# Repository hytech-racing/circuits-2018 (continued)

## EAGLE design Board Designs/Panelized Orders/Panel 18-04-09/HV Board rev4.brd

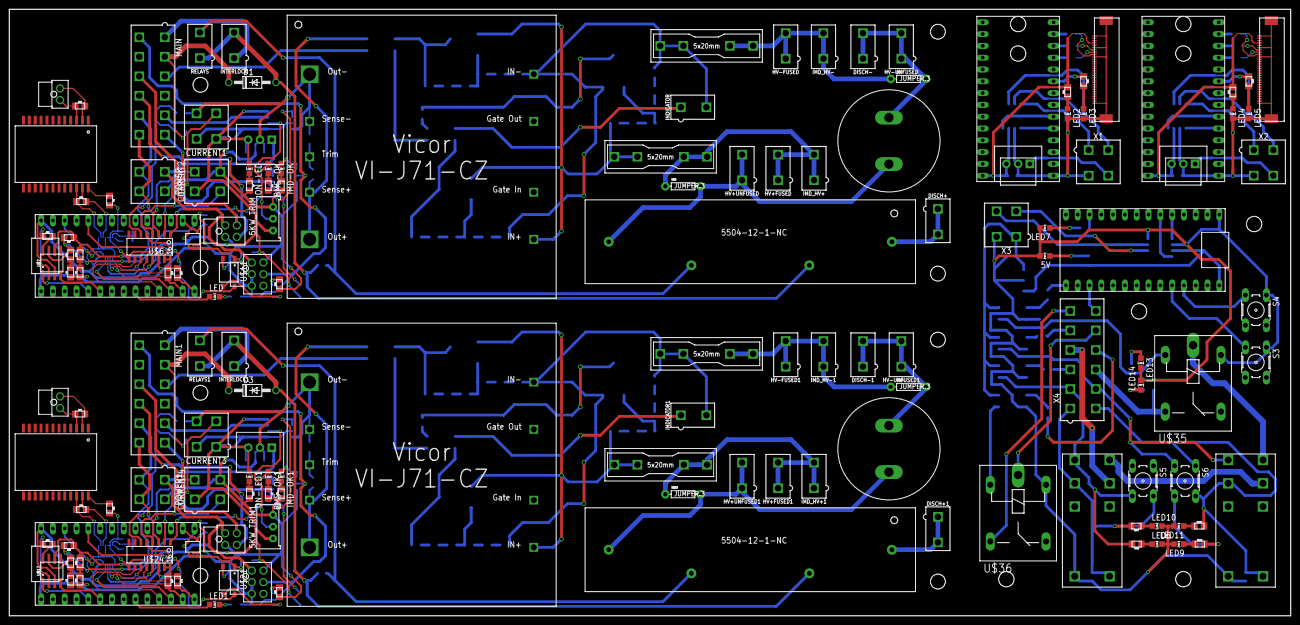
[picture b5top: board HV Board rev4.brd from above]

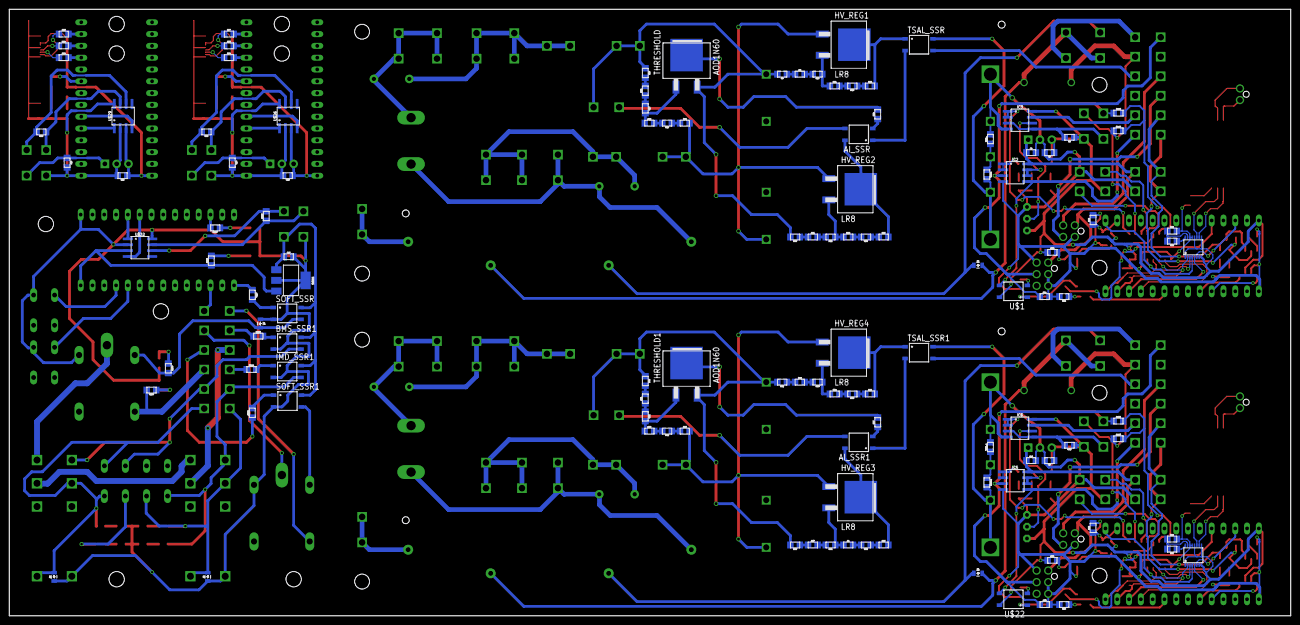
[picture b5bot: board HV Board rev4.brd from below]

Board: 2 copper layers, 275.8 x 130.6 mm, 262 parts (117 on the bottom side), 235 nets.

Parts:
5KW_TRIM, 5KW_TRIM1: TRIMPOT_3296
5V: LED-805
5VREG: SOT223
AI_SSR, AI_SSR1: CPC1002N; SOP04
BMS-OK, BMS-OK1: GREEN; LED-805
BMS_SSR1: CPC1002N; SOP04
C1, C6: 220uF; LLS2V221MELZ
C2, C3, C5, C12: 10uF; 0805
C4, C11: 27pF; 0805
C7, C8, C9, C10: 560pF; 0805
C13, C15: 0.1uF; 0805
C14, C16: 0.33uF; 0805
C17: .22uF; 0805
CURRENT1, CURRENT2, CURRENT3, CURRENT4: CONNECTOR-4; MINIFIT_5566-4
D1, D3: DIODE; DO-41
D2, D4, D5, D6, D7: DIODE0805; 0805_D
DISCH+, DISCH+1: DISCHARGE+; MINIFIT_5566-2
DISCH-, DISCH-1: DISCHARGE -; MINIFIT_5566-2
EM, EM1: CONNECTOR-4; NANO-FIT_VERTICAL-4
FUSE, FUSE1, FUSE2, FUSE3: 1A; 0751.0110
HV+FUSED, HV+FUSED1: FUSED+; MINIFIT_5566-2
HV+UNFUSED, HV+UNFUSED1: FSAE; MINIFIT_5566-2
HV-FUSED, HV-FUSED1: FUSED-; MINIFIT_5566-2
HV-UNFUSED, HV-UNFUSED1: FSAE; MINIFIT_5566-2
HV_REG1, HV_REG2, HV_REG3, HV_REG4: LR8; TO-252
IC1, IC4: OKI-78SR
IC2, IC3, IC5, IC6: NE5532SOIC; SOIC-08
IC7, IC8: TO-220
IMD, IMD1: CONNECTOR-6; NANO-FIT_VERTICAL-6
IMD-OK, IMD-OK1: YELLOW; LED-805
IMD_HV+, IMD_HV+1: IMD+; MINIFIT_5566-2
IMD_HV-, IMD_HV-1: IMD-; MINIFIT_5566-2
IMD_SSR1: CPC1002N; SOP04
INDICATOR, INDICATOR1: INDICATOR; MINIFIT_5566-2
INTERLOCK, INTERLOCK1: MINIFIT_5566-2
ISOSPI, ISOSPI1: CONNECTOR-2; NANO-FIT_VERTICAL-2
LED, LED1: BLUE; LED-805
LED2, LED3, LED4, LED5, LED6, LED7, LED9, LED10, LED11, LED13, LED14: LED-805
MAIN, MAIN1: CONNECTOR-12; MINIFIT_5566-12
ON-LED, ON-LED1: PURPLE; LED-805
POWER, POWER1: CONNECTOR-4; MINIFIT_5566-4
R1, R11, R12, R13, R23, R24, R25, R36, R37, R41, R48, R53, R54, R55, R56, R70, R71, R75: 2k; 0805
R2, R3, R4, R7: 820; 0805
R5, R44: 270; 0805
R6, R42, R43, R76: 10k; 0805
R8, R9, R10, R59, R60, R61: 8.2k; 0805
R14, R15, R16, R45, R49, R50: 510k; 0805
R17, R18, R19, R46, R51, R52, R118, R120: 43k; 0805
R20, R21, R22, R32, R57, R58: 20k; 0805
R26, R30, R33, R34, R47, R65, R67, R68: 1k; 0805
R27, R35, R62, R69, R80, R86, R113: 120; 0805
R28, R29, R40, R63, R64, R74: 100; 0805
R31, R66: 43; 0805
R38, R72: 430; 0805
R39, R73: 200; 0805
R77, R78, R79, R81, R82, R83, R84, R85, R87, R88, R105, R106, R107, R108, R109, R110, R111, R112, R114, R115, R116, R117: 0805
R119, R121: 12k; 0805
RELAYS, RELAYS1: MINIFIT_5566-2
S3, S4, S5, S6: B3F-10XX
SOFT_SSR, SOFT_SSR1: CPC1002N; SOP04
THRESHOLD, THRESHOLD1: AOD1N60; TO-252
TRIM+, TRIM+1: 0805
TRIM-, TRIM-1: 0805
TSAL_SSR, TSAL_SSR1: CPC1002N; SOP04
U$1, U$11, U$21, U$22: SOP04
U$2, U$23: SM51589PEL
U$3, U$4, U$15, U$16: JUMPER.3; AXIAL-0.3
U$5, U$14: HV_DCDC_VI-J71-CZ
U$6, U$24: MCP3208SOIC; SOIC-16
U$7, U$17, U$26, U$29, U$32: MCP2551; SOIC-08
U$8, U$18: LTC6820; MSOP-16
U$9, U$19, U$25, U$28, U$31: TEENSY_3.2_SIMPLE
U$10, U$20: STWD100; SOT23-5
U$12, U$13: 5504-12-1-NC
U$27, U$30: FFC-30P-0.5MM
U$33, U$34: G2RL-2-DC12; G2RL-2
U$35, U$36: G5LE; ZF112
X1, X2, X3: CONNECTOR-4; MINIFIT_5566-4
X4: CONNECTOR-12; MINIFIT_5566-12

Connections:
5KW_TRIG: 5KW_TRIM.2, IC3.6
5KW_TRIG1: 5KW_TRIM1.2, IC6.6
+3V1: U$18.6, U$19.3.3V
+3V3: U$8.6, U$9.3.3V
+5V: 5KW_TRIM.1, C3.1, CURRENT1.1, CURRENT2.1, IC1.3, IC3.8, ON-LED.A, R6.1, R36.1, R37.1, R38.1, U$1.4, U$6.5, U$6.15, U$6.16, U$7.3, U$8.1, U$8.7, U$8.8, U$8.9, U$8.12, U$9.VIN, U$10.VCC
+5V1: 5KW_TRIM1.1, C5.1, CURRENT3.1, CURRENT4.1, IC4.3, IC6.8, ON-LED1.A, R43.1, R70.1, R71.1, R72.1, U$17.3, U$18.1, U$18.7, U$18.8, U$18.9, U$18.12, U$19.VIN, U$20.VCC, U$22.4, U$24.5, U$24.15, U$24.16
+5V2: C13.1, IC7.3, R81.2, U$25.VIN, U$26.3, U$27.26, U$27.27
+5V3: C15.1, IC8.3, R87.2, U$28.VIN, U$29.3, U$30.26, U$30.27
+5V4: 5VREG.3, R106.1, U$31.VIN, U$32.3
+12V: C2.1, EM.P$1, IC1.1, IC2.8, IMD.P$1, POWER.1
+12V1: C12.1, EM1.P$1, IC4.1, IC5.8, IMD1.P$1, POWER1.1
+12V2: C14.1, IC7.1, X1.4
+12V3: C16.1, IC8.1, X2.4
+12V4: 5VREG.1, BMS_SSR1.4, C17.1, IMD_SSR1.4, SOFT_SSR.4, SOFT_SSR1.4, X3.1
BMS_12V: BMS_SSR1.3, R112.2, S6.3, S6.4, U$34.4, X4.8
BMS_INRLK: R116.1, X4.10
BMS_OK: IC2.5, MAIN.6, U$1.3
BMS_OK1: IC5.5, MAIN1.6, U$22.3
BMS_OK2: D6.C, R108.2, S6.1, S6.2, U$34.3, U$34.COIL-, X4.7
BMS_WATCH: U$1.1, U$11.3
BMS_WATCH1: U$21.3, U$22.1
BSPD_CUR_FAULT: IC3.7, MAIN.5
BSPD_CUR_FAULT1: IC6.7, MAIN1.5
BTN_X: S4.3, U$31.A9
BTN_Y: S3.3, U$31.A8
CANH: MAIN.12, POWER.4, R27.2, R28.2, U$7.7
CANH1: MAIN1.12, POWER1.4, R62.2, R63.2, U$17.7
CANH2: R80.1, U$26.7, X1.1
CANH3: R86.1, U$29.7, X2.1
CANH4: R113.1, U$32.7, X3.4
CANL: MAIN.11, POWER.3, R27.1, R29.2, U$7.6
CANL1: MAIN1.11, POWER1.3, R62.1, R64.2, U$17.6
CANL2: R80.2, U$26.6, X1.2
CANL3: R86.2, U$29.6, X2.2
CANL4: R113.2, U$32.6, X3.3
CANRX: U$25.D4(CANRX), U$26.4
CANRX1: U$28.D4(CANRX), U$29.4
CANRX2: U$31.D4(CANRX), U$32.4
CANTX: U$25.D3(CANTX), U$26.1
CANTX1: U$28.D3(CANTX), U$29.1
CANTX2: U$31.D3(CANTX), U$32.1
CS_LTC1: U$18.5, U$19.D10(TX2)
CS_LTC6820: U$8.5, U$9.D10(TX2)
CS_MCP1: U$19.D9(RX2), U$24.10
CS_MCP3208: U$6.10, U$9.D9(RX2)
CUR_SENSE_1: IC3.1, IC3.2, U$6.1
CUR_SENSE_1_RAW: CURRENT1.2, IC3.3, IC3.5, R6.2
CUR_SENSE_1_RAW1: CURRENT3.2, IC6.3, IC6.5, R43.2
CUR_SENSE_2: CURRENT2.2, U$6.3
CUR_SENSE_3: CURRENT4.2, U$24.3
CUR_SENSE_4: IC6.1, IC6.2, U$24.1
DISCHARGE_RELAY_GND: D2.A, RELAYS.2, U$12.COIL-
DISCHARGE_RELAY_GND1: D4.A, RELAYS1.2, U$13.COIL-
EM_IO1: EM.P$3, MAIN.9
EM_IO2: EM.P$4, MAIN.10
EM_IO3: EM1.P$3, MAIN1.9
EM_IO4: EM1.P$4, MAIN1.10
GND: 5KW_TRIM.3, C2.2, C3.2, C4.2, C8.1, C9.1, CURRENT1.4, CURRENT2.4, EM.P$2, IC1.2, IC2.4, IC3.4, IMD.P$2, IMD.P$3, IMD.P$4, POWER.2, R3.1, R4.2, R5.2, R30.1, R31.2, R34.2, R39.1, R41.2, R42.2, R119.1, TRIM-.2, U$5.8SENSE-, U$5.9VOUT-, U$6.9, U$6.14, U$7.2, U$8.13, U$8.14, U$9.GND, U$10.EN, U$10.GND, U$11.2
GND1: 5KW_TRIM1.3, C5.2, C7.1, C10.1, C11.2, C12.2, CURRENT3.4, CURRENT4.4, EM1.P$2, IC4.2, IC5.4, IC6.4, IMD1.P$2, IMD1.P$3, IMD1.P$4, POWER1.2, R2.1, R7.2, R44.2, R65.1, R66.2, R68.2, R73.1, R75.2, R76.2, R121.1, TRIM-1.2, U$14.8SENSE-, U$14.9VOUT-, U$17.2, U$18.13, U$18.14, U$19.GND, U$20.EN, U$20.GND, U$21.2, U$24.9, U$24.14
GND2: C13.2, C14.2, IC7.2, LED2.C, LED3.C, U$25.GND, U$26.2, U$26.8, U$27.1, U$27.21, U$27.25, U$27.30, U$27.PAD@0, U$27.PAD@1, X1.3
GND3: C15.2, C16.2, IC8.2, LED4.C, LED5.C, U$28.GND, U$29.2, U$29.8, U$30.1, U$30.21, U$30.25, U$30.30, U$30.PAD@0, U$30.PAD@1, X2.3
GND4: 5V.C, 5VREG.2, 5VREG.4, BMS_SSR1.2, C17.2, D5.A, D6.A, D7.A, IMD_SSR1.2, LED6.C, LED7.C, LED9.C, LED10.C, LED11.C, LED13.C, LED14.C, S3.1, S4.1, SOFT_SSR.2, SOFT_SSR1.2, U$31.GND, U$32.2, U$32.8, U$33.COIL+, U$34.COIL+, U$35.1, U$36.1, X3.2
GPIO: U$31.A1, X4.12
HV+FUSED: FUSE.L1, FUSE.L2, HV+FUSED.1, HV+FUSED.2, IMD_HV+.1, IMD_HV+.2, U$3.P$1
HV+FUSED1: FUSE2.L1, FUSE2.L2, HV+FUSED1.1, HV+FUSED1.2, IMD_HV+1.1, IMD_HV+1.2, U$15.P$1
HV+FUSED_1A: FUSE.R1, FUSE.R2, HV_REG1.1, HV_REG2.1, R14.2, U$5.1VIN+
HV+FUSED_1A1: FUSE2.R1, FUSE2.R2, HV_REG3.1, HV_REG4.1, R50.2, U$14.1VIN+
HV+UNFUSED_FSAE: C1.P$1, HV+UNFUSED.1, HV+UNFUSED.2, U$3.P$2, U$12.CONTACT1
HV+UNFUSED_FSAE1: C6.P$1, HV+UNFUSED1.1, HV+UNFUSED1.2, U$13.CONTACT1, U$15.P$2
HV+UNFUSED_FSAE_DISCHARGE: DISCH+.1, DISCH+.2, U$12.CONTACT2
HV+UNFUSED_FSAE_DISCHARGE1: DISCH+1.1, DISCH+1.2, U$13.CONTACT2
HV-FUSED: FUSE1.L1, FUSE1.L2, HV-FUSED.1, HV-FUSED.2, IMD_HV-.1, IMD_HV-.2, U$4.P$1
HV-FUSED1: FUSE3.L1, FUSE3.L2, HV-FUSED1.1, HV-FUSED1.2, IMD_HV-1.1, IMD_HV-1.2, U$16.P$1
HV-FUSED_1A: FUSE1.R1, FUSE1.R2, INDICATOR.2, R8.2, R19.1, R20.2, THRESHOLD.3, U$5.4VIN-
HV-FUSED_1A1: FUSE3.R1, FUSE3.R2, INDICATOR1.2, R46.1, R58.2, R61.2, THRESHOLD1.3, U$14.4VIN-
HV-UNFUSED_FSAE: C1.P$2, DISCH-.1, DISCH-.2, HV-UNFUSED.1, HV-UNFUSED.2, U$4.P$2
HV-UNFUSED_FSAE1: C6.P$2, DISCH-1.1, DISCH-1.2, HV-UNFUSED1.1, HV-UNFUSED1.2, U$16.P$2
IMD_12V: IMD_SSR1.3, R111.2, S5.3, S5.4, U$33.4, X4.2
IMD_OK: D5.C, R107.2, S5.1, S5.2, U$33.3, U$33.COIL-, X4.1
ISOSPI-M: ISOSPI.P$2, R40.1, U$2.3
ISOSPI-M1: ISOSPI1.P$2, R74.1, U$23.3
ISOSPI-P: ISOSPI.P$1, R40.2, U$2.2
ISOSPI-P1: ISOSPI1.P$1, R74.2, U$23.2
MISO: R37.2, U$6.12, U$8.3, U$9.D12
MISO1: R71.2, U$18.3, U$19.D12, U$24.12
MOSI: R36.2, U$6.11, U$8.2, U$9.D11
MOSI1: R70.2, U$18.2, U$19.D11, U$24.11
unnamed: AI_SSR.4, HV_REG2.2(TAB), R25.2
unnamed: HV_REG1.2(TAB), R13.2, TSAL_SSR.1
unnamed: ON-LED.C, R5.1
unnamed: R39.2, U$1.2
unnamed: AI_SSR.2, R26.1
unnamed: AI_SSR.1, TSAL_SSR.2
unnamed: AI_SSR.3, INDICATOR.1
unnamed: R8.1, R9.1
unnamed: R26.2, THRESHOLD.2(TAB)
unnamed: R14.1, R15.1
unnamed: R15.2, R16.2
unnamed: R17.1, R18.1
unnamed: R18.2, R19.2
unnamed: R9.2, R10.2
unnamed: HV_REG2.3, R22.1, R23.1
unnamed: R11.2, R12.2
unnamed: R12.1, R13.1
unnamed: HV_REG1.3, R10.1, R11.1
unnamed: R23.2, R24.2
unnamed: R24.1, R25.1
unnamed: R21.2, R22.2
unnamed: R16.1, R17.2, THRESHOLD.1
unnamed: R20.1, R21.1
unnamed: AI_SSR1.4, HV_REG3.2(TAB), R56.2
unnamed: U$7.1, U$9.D3(CANTX)
unnamed: R30.2, U$7.8
unnamed: C8.2, R28.1
unnamed: C9.2, R29.1
unnamed: LED.C, R31.1
unnamed: HV_REG3.3, R1.1, R32.1
unnamed: R33.1, U$8.16
unnamed: R33.2, R34.1, U$8.15
unnamed: R35.1, U$2.22, U$8.10
unnamed: R35.2, U$2.23, U$8.11
unnamed: C4.1, U$2.24
unnamed: U$7.4, U$9.D4(CANRX)
unnamed: LED.A, U$9.D7(RX3)
unnamed: R38.2, U$10.WDO, U$11.1
unnamed: IC5.1, IC5.2, IMD-OK1.A
unnamed: U$9.A8, U$11.4
unnamed: BMS-OK1.A, IC5.6, IC5.7
unnamed: IC2.1, IC2.2, IMD-OK.A
unnamed: BMS-OK.A, IC2.6, IC2.7
unnamed: BMS-OK.C, R4.1
unnamed: IMD-OK.C, R3.2
unnamed: BMS-OK1.C, R7.1
unnamed: IMD-OK1.C, R2.2
unnamed: ON-LED1.C, R44.1
unnamed: HV_REG4.2(TAB), R48.2, TSAL_SSR1.1
unnamed: R42.1, U$9.A0, U$10.WDI
unnamed: R49.1, R50.1
unnamed: R45.2, R49.2
unnamed: R51.1, R52.1
unnamed: R46.2, R51.2
unnamed: AI_SSR1.2, R47.1
unnamed: AI_SSR1.1, TSAL_SSR1.2
unnamed: AI_SSR1.3, INDICATOR1.1
unnamed: HV_REG4.3, R54.1, R59.1
unnamed: R59.2, R60.2
unnamed: R60.1, R61.1
unnamed: R45.1, R52.2, THRESHOLD1.1
unnamed: R53.2, R54.2
unnamed: R48.1, R53.1
unnamed: R47.2, THRESHOLD1.2(TAB)
unnamed: R1.2, R55.2
unnamed: R55.1, R56.1
unnamed: R32.2, R57.2
unnamed: R57.1, R58.1
unnamed: U$17.1, U$19.D3(CANTX)
unnamed: R65.2, U$17.8
unnamed: C7.2, R63.1
unnamed: C10.2, R64.1
unnamed: LED1.C, R66.1
unnamed: R67.1, U$18.16
unnamed: R67.2, R68.1, U$18.15
unnamed: R69.1, U$18.10, U$23.22
unnamed: R69.2, U$18.11, U$23.23
unnamed: C11.1, U$23.24
unnamed: U$17.4, U$19.D4(CANRX)
unnamed: LED1.A, U$19.D7(RX3)
unnamed: R72.2, U$20.WDO, U$21.1
unnamed: U$19.A8, U$21.4
unnamed: R76.1, U$19.A0, U$20.WDI
unnamed: R73.2, U$22.2
unnamed: LED2.A, R81.1
unnamed: R82.1, U$25.D7(RX3)
unnamed: LED3.A, R82.2
unnamed: LED4.A, R87.1
unnamed: R88.1, U$28.D7(RX3)
unnamed: LED5.A, R88.2
unnamed: LED6.A, R111.1
unnamed: LED10.A, R107.1
unnamed: LED11.A, R108.1
unnamed: LED13.A, R109.1
unnamed: LED14.A, R110.1
unnamed: LED9.A, R112.1
unnamed: SOFT_SSR1.3, U$36.2
unnamed: LED7.A, R105.1
unnamed: R105.2, U$31.D10(TX2)
unnamed: 5V.A, R106.2
unnamed: U$36.P, X4.11
unnamed: U$36.S, X4.6
unnamed: IMD_SSR1.1, R114.2
unnamed: BMS_SSR1.1, R115.2
unnamed: R114.1, X4.3
unnamed: R115.1, X4.5
unnamed: R116.2, SOFT_SSR1.1
unnamed: R117.1, U$31.D13
unnamed: R118.2, R119.2, U$6.6
unnamed: R120.2, R121.2, U$24.6
OKHS: IC2.3, IMD.P$5, MAIN.7, R41.1
OKHS1: IC5.3, IMD1.P$5, MAIN1.7, R75.1
RESET: R77.1, U$27.22
RESET1: R83.1, U$30.22
RX0: R79.1, U$27.23
RX1: R85.1, U$30.23
SCK: U$6.13, U$8.4, U$9.D13
SCK1: U$18.4, U$19.D13, U$24.13
SHUTDOWN1: D3.A, D4.C, INTERLOCK1.2, RELAYS1.1, U$13.COIL+
SHUTDOWN2: INTERLOCK1.1, MAIN1.1
SHUTDOWN6: INTERLOCK.1, MAIN.1
SHUTDOWN7: D1.A, D2.C, INTERLOCK.2, RELAYS.1, U$12.COIL+
SHUTDOWN7_EXT_OUT: D1.C, MAIN.2, R118.1
SHUTDOWN7_EXT_OUT1: D3.C, MAIN1.2, R120.1
SHUTDOWN_IN: U$33.6, X4.4
SHUTDOWN_IN_A: U$33.5, U$34.6
SHUTDOWN_IN_B: U$34.5, U$35.P
SHUTDOWN_OUT: R110.2, U$35.S, X4.9
SW_KILL: R117.2, SOFT_SSR.1
SW_KILL_RELAY: D7.C, R109.2, SOFT_SSR.3, U$35.2
TEMP_SENSE_1: CURRENT1.3, U$6.2
TEMP_SENSE_2: CURRENT2.3, U$6.4
TEMP_SENSE_3: CURRENT4.3, U$24.4
TEMP_SENSE_4: CURRENT3.3, U$24.2
TRIM: TRIM+.1, TRIM-.1, U$5.7TRIM
TRIM1: TRIM+1.1, TRIM-1.1, U$14.7TRIM
TSAL+: MAIN.3, TSAL_SSR.3
TSAL+1: MAIN1.3, TSAL_SSR1.3
TSAL_1: TRIM+.2, TSAL_SSR.4, U$5.5VOUT+, U$5.6SENSE+
TSAL_2: TRIM+1.2, TSAL_SSR1.4, U$14.5VOUT+, U$14.6SENSE+
TX0: R78.1, U$27.24
TX1: R84.1, U$30.24
UC_RST: R77.2, U$25.D11
UC_RST1: R83.2, U$28.D11
UC_RX: R79.2, U$25.D9(RX2)
UC_RX1: R85.2, U$28.D9(RX2)
UC_TX: R78.2, U$25.D10(TX2)
UC_TX1: R84.2, U$28.D10(TX2)

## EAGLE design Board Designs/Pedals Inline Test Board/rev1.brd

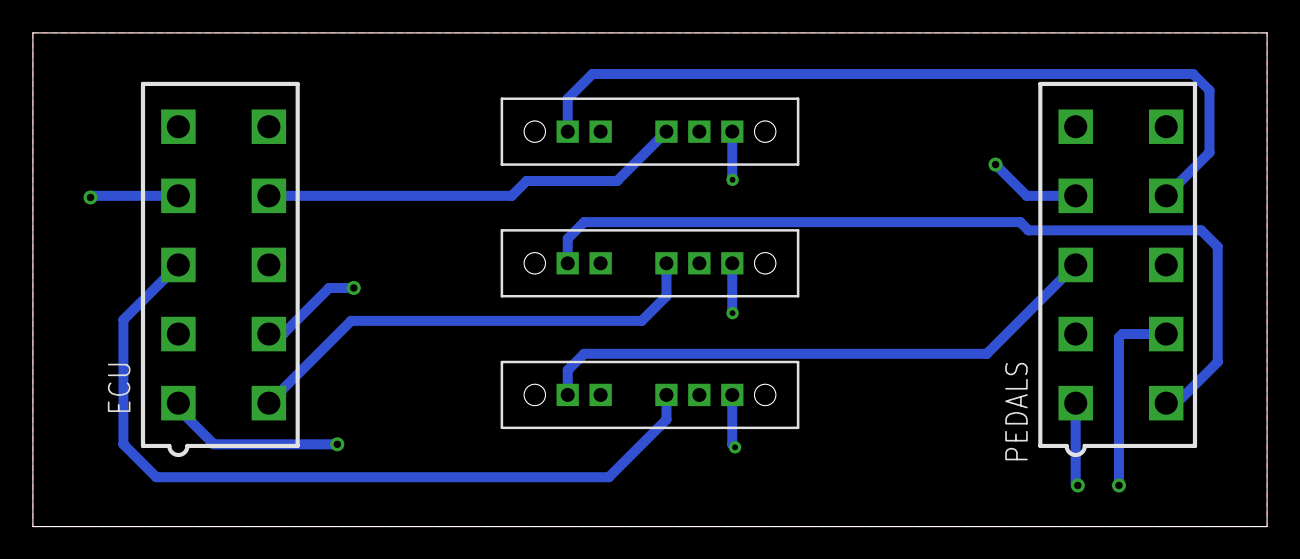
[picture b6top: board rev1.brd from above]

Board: 2 copper layers, 75.0 x 30.0 mm, 5 parts (0 on the bottom side), 8 nets.

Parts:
ECU: CONNECTOR-10; MINIFIT_5566-10
PEDALS: CONNECTOR-10; MINIFIT_5566-10
U$1, U$2, U$3: SS-14D0839-VG5PA

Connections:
+5V: ECU.1, ECU.4, ECU.7, PEDALS.1, PEDALS.4, PEDALS.7, U$1.4, U$2.4, U$3.4
GND: ECU.2, ECU.5, ECU.8, PEDALS.2, PEDALS.5, PEDALS.8, U$1.3, U$2.3, U$3.3
unnamed: ECU.9, U$1.COM
unnamed: ECU.6, U$2.COM
unnamed: ECU.3, U$3.COM
unnamed: PEDALS.9, U$1.1
unnamed: PEDALS.6, U$2.1
unnamed: PEDALS.3, U$3.1

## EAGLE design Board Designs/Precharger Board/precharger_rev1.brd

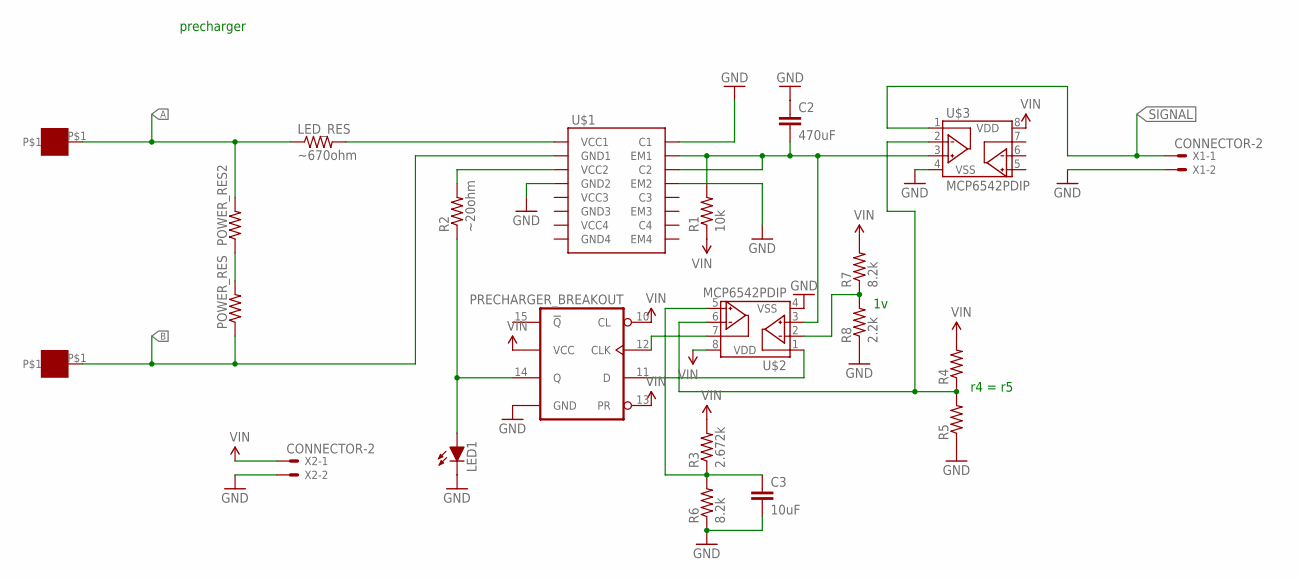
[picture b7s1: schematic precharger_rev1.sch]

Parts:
+: SOLDER_PAD; SOLDER_PAD_XSMALL
-: SOLDER_PAD; SOLDER_PAD_XSMALL
C2: 470uF; CAP-PTH-5MM
C3: 10uF; CAP-PTH-5MM
LED1: LED-3MM
LED_RES: ~670ohm; AXIAL-0.3
POWER_RES, POWER_RES2: RESISTOR10W; 10W_RESISTOR_VISHAY
R1: 10k; AXIAL-0.3
R2: ~20ohm; AXIAL-0.3
R3: 2.672k; AXIAL-0.3
R4, R5: RESISTORAXIAL-0.3; AXIAL-0.3
R6, R7: 8.2k; AXIAL-0.3
R8: 2.2k; AXIAL-0.3
U$1: PRECHARGER_BREAKOUT
U$2, U$3: MCP6542PDIP; DIL08
X1, X2: CONNECTOR-2; MINIFIT_5566-2

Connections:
A1: +.P$1, LED_RES.P$1 (1), POWER_RES2.2
B: -.P$1, POWER_RES.1, U$1.2 (GND1)
GND: C2.1, C3.2, LED1.K (C), R5.P$1 (1), R6.P$1 (1), R8.P$1 (1), U$1.4 (GND2), U$1.16 (GND), U$1.29 (EM2), U$1.32 (C1), U$2.4 (VSS), U$3.4 (VSS), X1.2, X2.2
unnamed: LED1.A, R2.P$1 (1), U$1.14 (Q)
unnamed: POWER_RES.2, POWER_RES2.1
unnamed: C3.1, R3.P$1 (1), R6.P$2 (2), U$2.5 (VINB+)
unnamed: LED_RES.P$2 (2), U$1.1 (VCC1)
unnamed: U$1.12 (CLK), U$2.7 (VOUTB)
unnamed: U$1.11 (D), U$2.1 (VOUTA)
unnamed: R4.P$1 (1), R5.P$2 (2), U$2.6 (VINB-), U$3.2 (VINA-)
unnamed: R7.P$1 (1), R8.P$2 (2), U$2.2 (VINA-)
unnamed: R2.P$2 (2), U$1.3 (VCC2)
NODE: C2.2, R1.P$2 (2), U$1.30 (C2), U$1.31 (EM1), U$2.3 (VINA+), U$3.3 (VINA+)
SIGNAL: U$3.1 (VOUTA), X1.1
VIN: R1.P$1 (1), R3.P$2 (2), R4.P$2 (2), R7.P$2 (2), U$1.10 (CL), U$1.13 (PR), U$1.23 (VCC), U$2.8 (VDD), U$3.8 (VDD), X2.1

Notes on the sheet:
precharger
r4 = r5

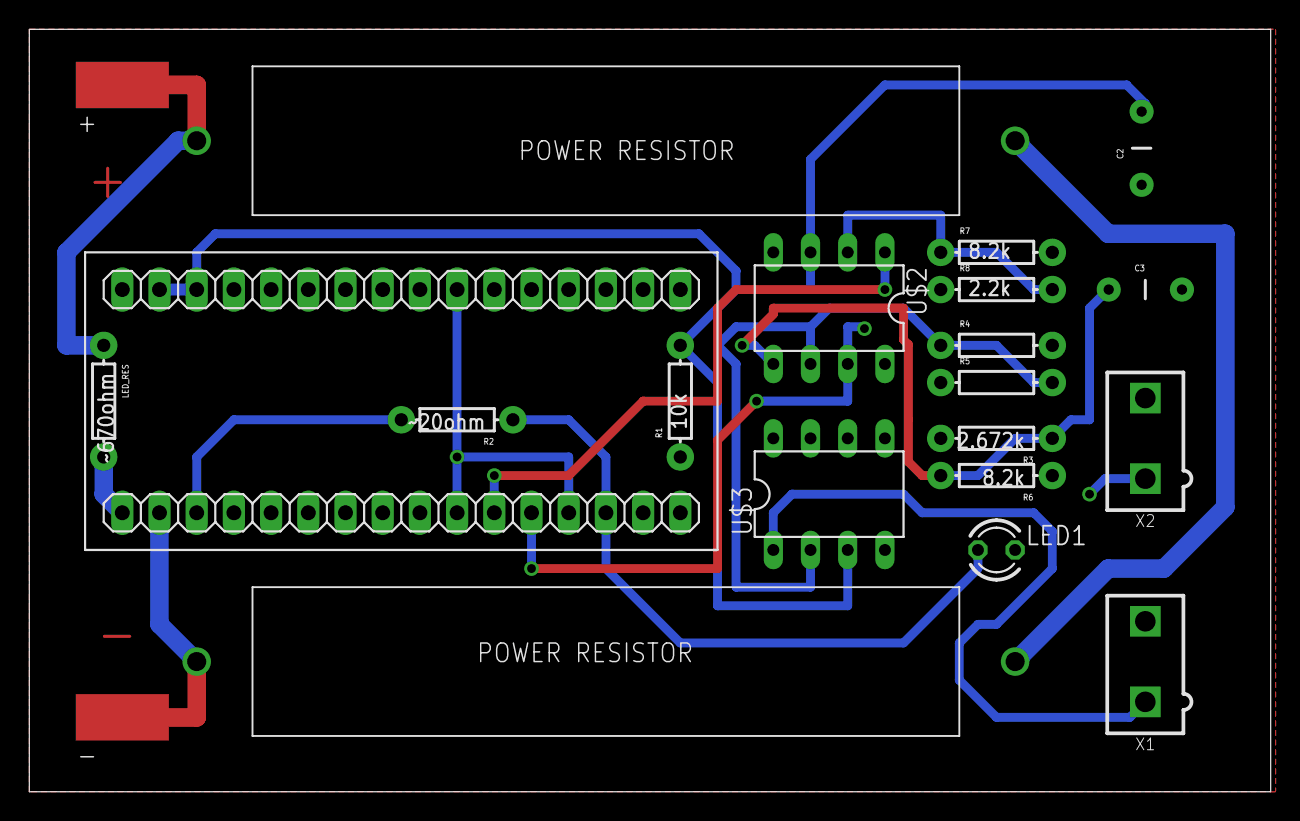
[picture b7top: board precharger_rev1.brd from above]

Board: 2 copper layers, 84.8 x 52.1 mm, 21 parts (0 on the bottom side), 15 nets.
